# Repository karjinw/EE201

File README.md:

# EE201
# aboutme
I like chicken
# aboutmee

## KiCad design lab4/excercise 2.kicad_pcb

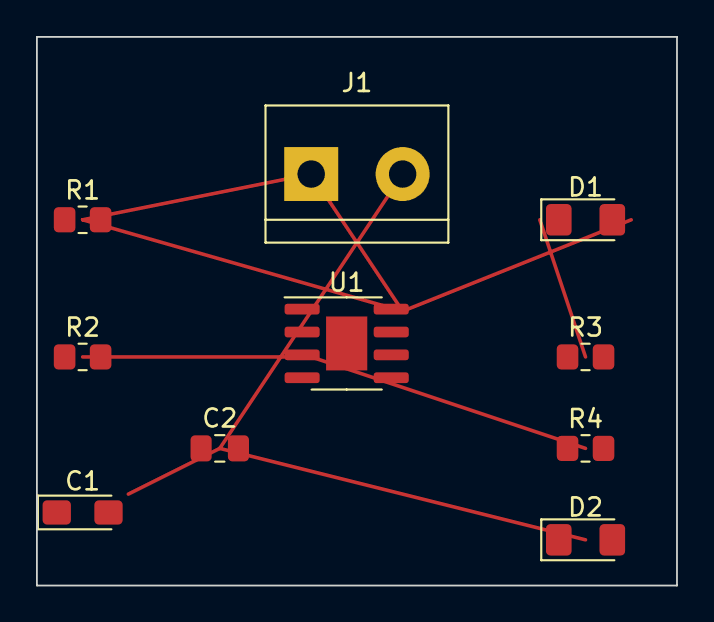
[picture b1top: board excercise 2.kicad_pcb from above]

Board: 2 copper layers, 35.6 x 30.5 mm, 10 parts (0 on the bottom side), 8 nets, no tracks yet.

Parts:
C1: 10 uF; CP_EIA-3216-18_Kemet-A_Pad1.58x1.35mm_HandSolder
C2: 0.01 uF; C_0805_2012Metric_Pad1.18x1.45mm_HandSolder
D1, D2: LED; LED_1206_3216Metric_Pad1.42x1.75mm_HandSolder
J1: Conn_01x02_Male; TerminalBlock_bornier-2_P5.08mm
R1, R3, R4: 1k; R_0805_2012Metric_Pad1.20x1.40mm_HandSolder
R2: 10k; R_0805_2012Metric_Pad1.20x1.40mm_HandSolder
U1: NE555D; SOIC-8-1EP_3.9x4.9mm_P1.27mm_EP2.29x3mm

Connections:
+9V: D1.2 (A), J1.1, R1.1, U1.4 (R), U1.8 (VCC)
/pin_2: C1.1, R2.2, U1.6 (THR)
/pin_3: R3.2, R4.1, U1.3 (Q)
/pin_7: R1.2, R2.1, U1.7 (DIS)
GND: C1.2, C2.2, D2.1 (K), J1.2, U1.1 (GND)
unnamed: C2.1, U1.5 (CV)
unnamed: D1.1 (K), R3.1
unnamed: D2.2 (A), R4.2

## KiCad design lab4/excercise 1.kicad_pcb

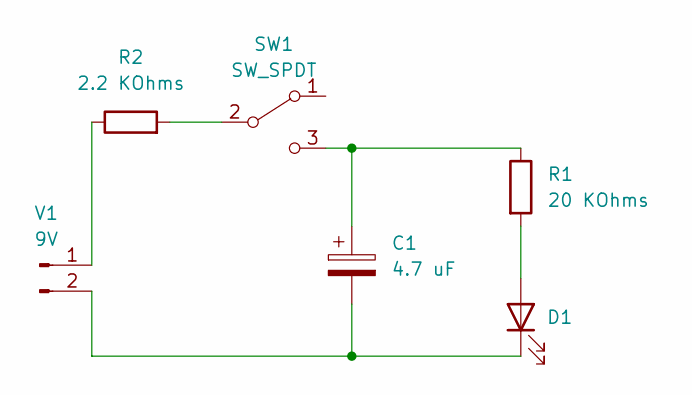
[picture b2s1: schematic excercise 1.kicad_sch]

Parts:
C1: 4.7 uF
D1: LED
R1: 20 KOhms
R2: 2.2 KOhms
SW1: SW_SPDT
V1: 9V

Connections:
unnamed: C1.1, R1.1, SW1.3 (C)
unnamed: C1.2, D1.1 (K), V1.2
unnamed: D1.2 (A), R1.2
unnamed: R2.1, V1.1
unnamed: R2.2, SW1.2 (B)

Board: 2 copper layers, 6 parts (0 on the bottom side), 5 nets, no tracks yet.

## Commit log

2023-02-10 odddd
2023-02-17 okdd
